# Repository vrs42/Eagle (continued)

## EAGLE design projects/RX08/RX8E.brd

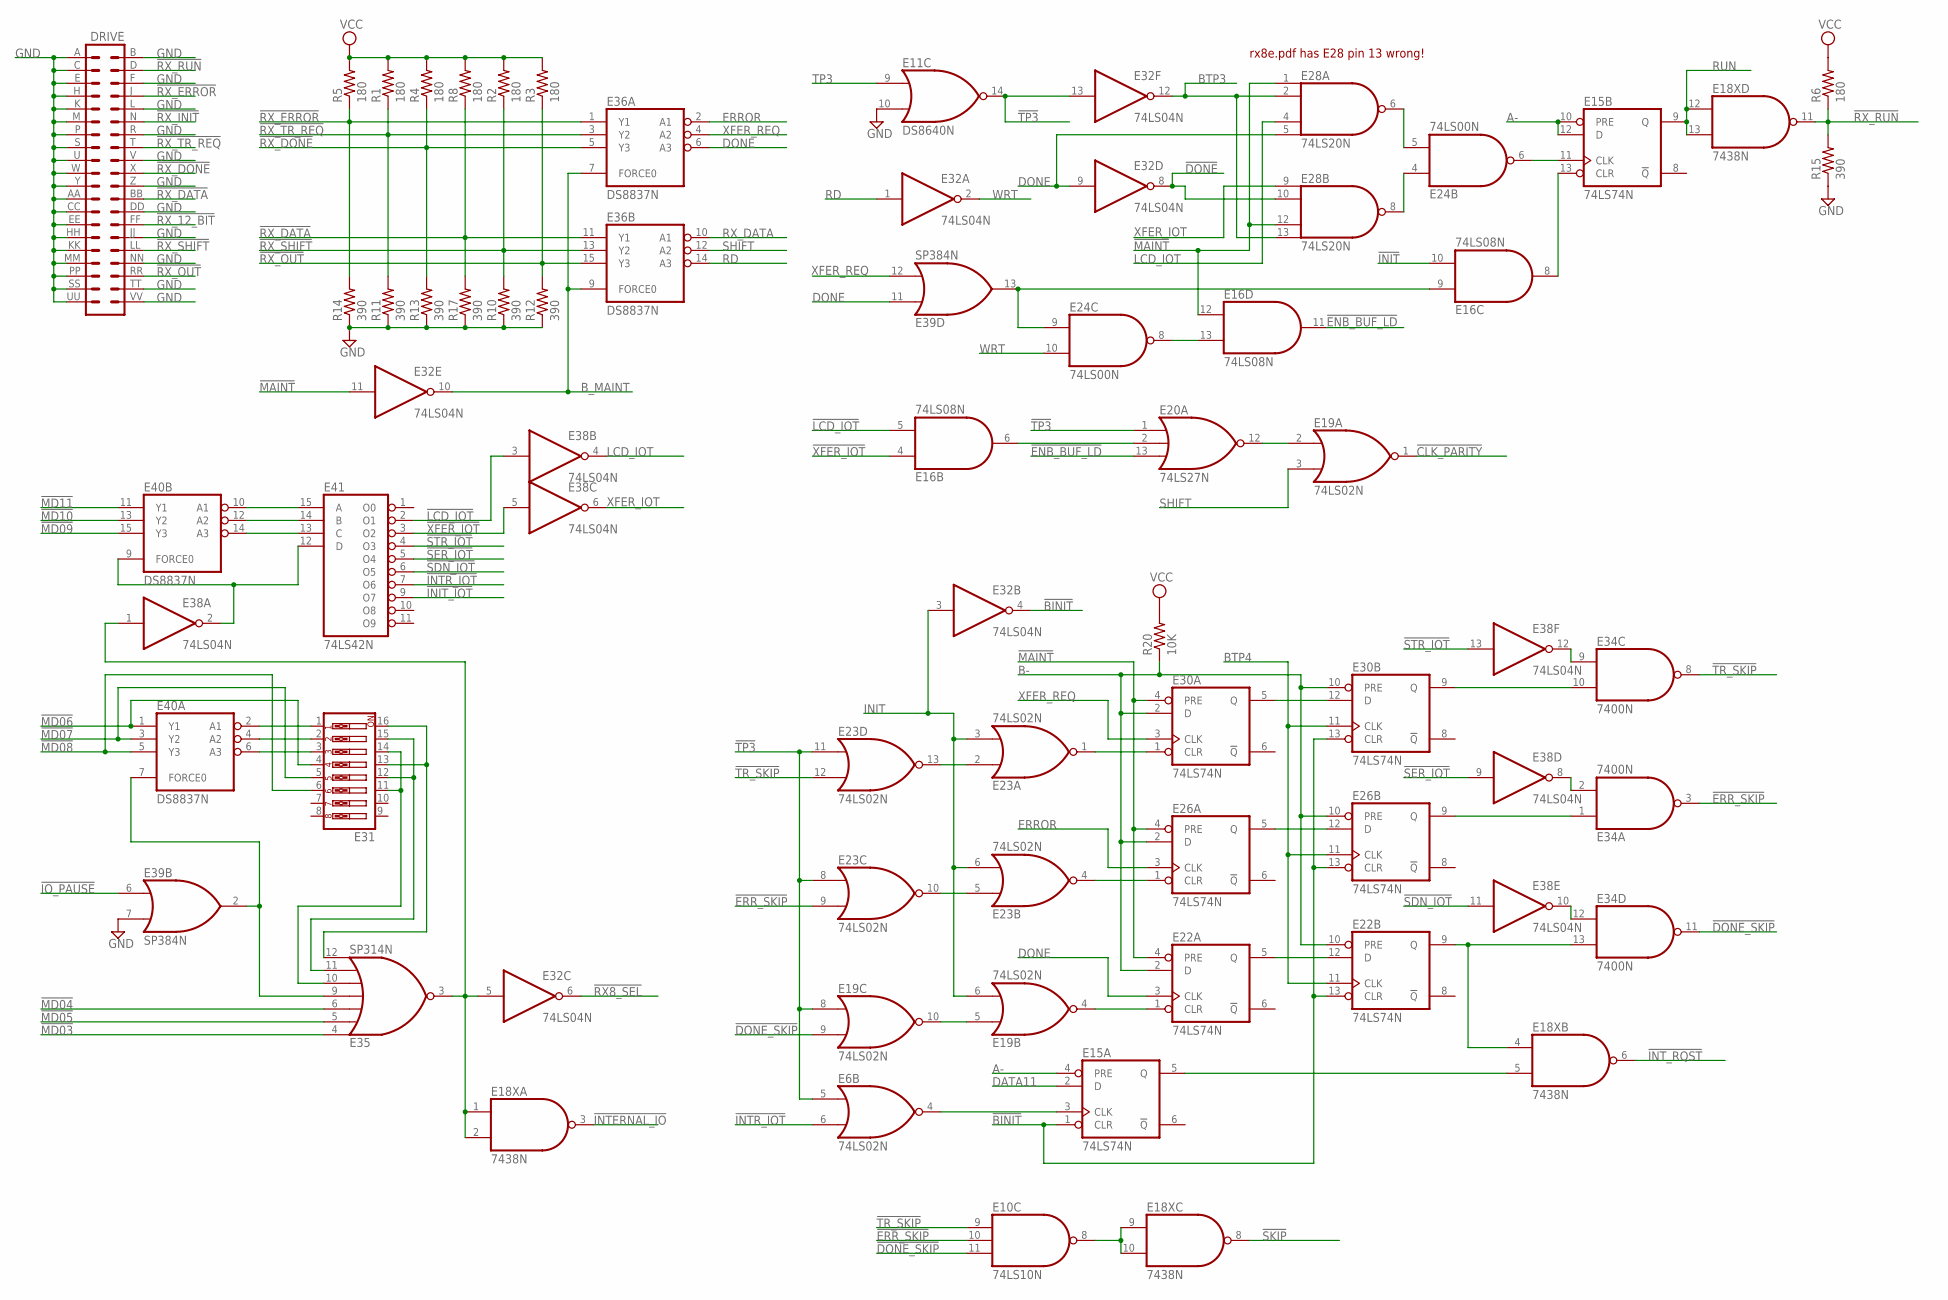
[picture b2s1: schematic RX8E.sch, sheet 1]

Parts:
DRIVE: DEC40PINH
E6, E19, E23: 74LS02N; DIL14
E10: 74LS10N; DIL14
E11: DS8640N; DIL14
E15, E22, E26, E30: 74LS74N; DIL14
E16: 74LS08N; DIL14
E18X: 7438N; DIL14
E20: 74LS27N; DIL14
E24: 74LS00N; DIL14
E28: 74LS20N; DIL14
E31: SW_DIP-8; EDG-08
E32, E38: 74LS04N; DIL14
E34: 7400N; DIL14
E35: SP314N; DIL14
E36, E40: DS8837N; DIL16
E39: SP384N; DIL14
E41: 74LS42N; DIL16
R1, R2, R3, R4, R5, R6, R8: 180; 0207/10
R10, R11, R12, R13, R14, R15, R17: 390; 0207/10
R20: 10K; 0207/10

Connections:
!BINIT: E15.1 (CLR), E22.13 (CLR), E26.13 (CLR), E30.13 (CLR), E32.4 (O)
!CLK_PARITY: E19.1 (O); also elsewhere on the board
!DONE: E28.10 (I1), E32.8 (O); also elsewhere on the board
!DONE_SKIP: E10.11 (I2), E19.9 (I1), E34.11 (O); also elsewhere on the board
!ENB_BUF_LD: E16.11 (O), E20.13 (I2); also elsewhere on the board
!ERR_SKIP: E10.10 (I1), E23.9 (I1), E34.3 (O)
!INIT: E16.10 (I1); also elsewhere on the board
!INIT_IOT: E41.9 (O7); also elsewhere on the board
!INTERNAL_IO: E18X.3 (O); also elsewhere on the board
!INTR_IOT: E6.6 (I1), E41.7 (O6)
!INT_RQST: E18X.6 (O); also elsewhere on the board
!IO_PAUSE: E39.6 (I0); also elsewhere on the board
!LCD_IOT: E16.5 (I1), E38.3 (I), E41.2 (O1); also elsewhere on the board
!MAINT: E16.12 (I0), E22.4 (PRE), E26.4 (PRE), E28.1 (I0), E28.12 (I2), E30.4 (PRE), E32.11 (I); also elsewhere on the board
!MD03: E35.4 (I0); also elsewhere on the board
!MD04: E35.6 (I2); also elsewhere on the board
!MD05: E35.5 (I1); also elsewhere on the board
!MD06: E31.4, E40.1 (Y1); also elsewhere on the board
!MD07: E31.5, E40.3 (Y2); also elsewhere on the board
!MD08: E31.6, E40.5 (Y3); also elsewhere on the board
!MD09: E40.15 (Y3); also elsewhere on the board
!MD10: E40.13 (Y2); also elsewhere on the board
!MD11: E40.11 (Y1); also elsewhere on the board
!RX8_SEL: E32.6 (O); also elsewhere on the board
!RX_12_BIT: DRIVE.FF (28); also elsewhere on the board
!RX_DATA: DRIVE.BB (24), E36.11 (Y1), R8.1, R17.2; also elsewhere on the board
!RX_DONE: DRIVE.X (20), E36.5 (Y3), R4.1, R13.2
!RX_ERROR: DRIVE.J (8), E36.1 (Y1), R5.1, R14.2
!RX_INIT: DRIVE.N (12); also elsewhere on the board
!RX_OUT: DRIVE.RR (36), E36.15 (Y3), R3.1, R12.2
!RX_RUN: DRIVE.D (4), E18X.11 (O), R6.1, R15.2
!RX_SHIFT: DRIVE.LL (32), E36.13 (Y2), R2.1, R10.2
!RX_TR_REQ: DRIVE.T (16), E36.3 (Y2), R1.1, R11.2
!SDN_IOT: E38.11 (I), E41.6 (O5)
!SER_IOT: E38.9 (I), E41.5 (O4)
!SKIP: E18X.8 (O); also elsewhere on the board
!STR_IOT: E38.13 (I), E41.4 (O3)
!TP3: E6.5 (I0), E11.14 (O), E19.8 (I0), E20.1 (I0), E23.8 (I0), E23.11 (I0), E32.13 (I); also elsewhere on the board
!TR_SKIP: E10.9 (I0), E23.12 (I1), E34.8 (O); also elsewhere on the board
!XFER_IOT: E16.4 (I0), E38.5 (I), E41.3 (O2); also elsewhere on the board
A-: E15.4 (PRE), E15.10 (PRE), E15.12 (D); also elsewhere on the board
B-: E22.2 (D), E22.10 (PRE), E26.2 (D), E26.10 (PRE), E30.2 (D), E30.10 (PRE), R20.1; also elsewhere on the board
BTP3: E28.2 (I1), E28.13 (I3), E32.12 (O); also elsewhere on the board
BTP4: E22.11 (CLK), E26.11 (CLK), E30.11 (CLK); also elsewhere on the board
B_MAINT: E32.10 (O), E36.7 (FORCE0), E36.9 (FORCE0)
DATA11: E15.2 (D); also elsewhere on the board
DONE: E22.3 (CLK), E28.5 (I3), E32.9 (I), E36.6 (A3), E39.11 (I0); also elsewhere on the board
ERROR: E26.3 (CLK), E36.2 (A1)
GND: DRIVE.A (1), DRIVE.AA (23), DRIVE.B (2), DRIVE.C (3), DRIVE.CC (25), DRIVE.DD (26), DRIVE.E (5), DRIVE.EE (27), DRIVE.F (6), DRIVE.H (7), DRIVE.HH (29), DRIVE.JJ (30), DRIVE.K (9), DRIVE.KK (31), DRIVE.L (10), DRIVE.M (11), DRIVE.MM (33), DRIVE.NN (34), DRIVE.P (13), DRIVE.PP (35), DRIVE.R (14), DRIVE.S (15), DRIVE.SS (37), DRIVE.TT (38), DRIVE.U (17), DRIVE.UU (39), DRIVE.V (18), DRIVE.VV (40), DRIVE.W (19), DRIVE.Y (21), DRIVE.Z (22), E6.7 (GND), E10.7 (GND), E11.1 (GND), E11.10 (I1), E15.7 (GND), E16.7 (GND), E18X.7 (GND), E19.7 (GND), E20.7 (GND), E22.7 (GND), E23.7 (GND), E24.7 (GND), E26.7 (GND), E28.7 (GND), E30.7 (GND), E32.7 (GND), E34.7 (GND), E35.1 (GND), E36.8 (GND), E38.7 (GND), E39.1 (GND), E39.7 (I1), E40.8 (GND), E41.8 (GND), R10.1, R11.1, R12.1, R13.1, R14.1, R15.1, R17.1; also elsewhere on the board
INIT: E19.6 (I1), E23.3 (I1), E23.6 (I1), E32.3 (I); also elsewhere on the board
LCD_IOT: E28.4 (I2), E38.4 (O); also elsewhere on the board
unnamed: E31.11, E31.14, E35.10 (I4)
unnamed: E31.12, E31.15, E35.11 (I5)
unnamed: E31.13, E31.16, E35.12 (I6)
unnamed: E31.3, E40.6 (A3)
unnamed: E31.2, E40.4 (A2)
unnamed: E31.1, E40.2 (A1)
unnamed: E35.9 (I3), E39.2 (O), E40.7 (FORCE0)
unnamed: E18X.1 (I0), E18X.2 (I1), E32.5 (I), E35.3 (O), E38.1 (I)
unnamed: E19.5 (I0), E19.10 (O)
unnamed: E38.2 (O), E40.9 (FORCE0), E41.12 (D)
unnamed: E40.14 (A3), E41.13 (C)
unnamed: E40.12 (A2), E41.14 (B)
unnamed: E40.10 (A1), E41.15 (A)
unnamed: E19.4 (O), E22.1 (CLR)
unnamed: E23.4 (O), E26.1 (CLR)
unnamed: E23.5 (I0), E23.10 (O)
unnamed: E23.2 (I0), E23.13 (O)
unnamed: E23.1 (O), E30.1 (CLR)
unnamed: E30.5 (Q), E30.12 (D)
unnamed: E26.5 (Q), E26.12 (D)
unnamed: E22.5 (Q), E22.12 (D)
unnamed: E18X.4 (I0), E22.9 (Q), E34.13 (I1)
unnamed: E26.9 (Q), E34.1 (I0)
unnamed: E6.4 (O), E15.3 (CLK)
unnamed: E30.9 (Q), E34.10 (I1)
unnamed: E34.2 (I1), E38.8 (O)
unnamed: E34.12 (I0), E38.10 (O)
unnamed: E34.9 (I0), E38.12 (O)
unnamed: E15.5 (Q), E18X.5 (I1)
unnamed: E10.8 (O), E18X.9 (I0), E18X.10 (I1)
unnamed: E24.5 (I1), E28.6 (O)
unnamed: E16.6 (O), E20.2 (I1)
unnamed: E24.4 (I0), E28.8 (O)
unnamed: E16.9 (I0), E24.9 (I0), E39.13 (O)
unnamed: E16.13 (I1), E24.8 (O)
unnamed: E15.13 (CLR), E16.8 (O)
unnamed: E19.2 (I0), E20.12 (O)
unnamed: E15.11 (CLK), E24.6 (O)
RD: E32.1 (I), E36.14 (A3); also elsewhere on the board
RUN: E15.9 (Q), E18X.12 (I0), E18X.13 (I1); also elsewhere on the board
RX_DATA: E36.10 (A1); also elsewhere on the board
SHIFT: E19.3 (I1), E36.12 (A2)
TP3: E11.9 (I0); also elsewhere on the board
VCC: E6.14 (VCC), E10.14 (VCC), E11.8 (VCC), E15.14 (VCC), E16.14 (VCC), E18X.14 (VCC), E19.14 (VCC), E20.14 (VCC), E22.14 (VCC), E23.14 (VCC), E24.14 (VCC), E26.14 (VCC), E28.14 (VCC), E30.14 (VCC), E32.14 (VCC), E34.14 (VCC), E35.8 (VCC), E36.16 (VCC), E38.14 (VCC), E39.8 (VCC), E40.16 (VCC), E41.16 (VCC), R1.2, R2.2, R3.2, R4.2, R5.2, R6.2, R8.2, R20.2; also elsewhere on the board
WRT: E24.10 (I1), E32.2 (O); also elsewhere on the board
XFER_IOT: E28.9 (I0), E38.6 (O); also elsewhere on the board
XFER_REQ: E30.3 (CLK), E36.4 (A2), E39.12 (I1)

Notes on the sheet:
rx8e.pdf has E28 pin 13 wrong!

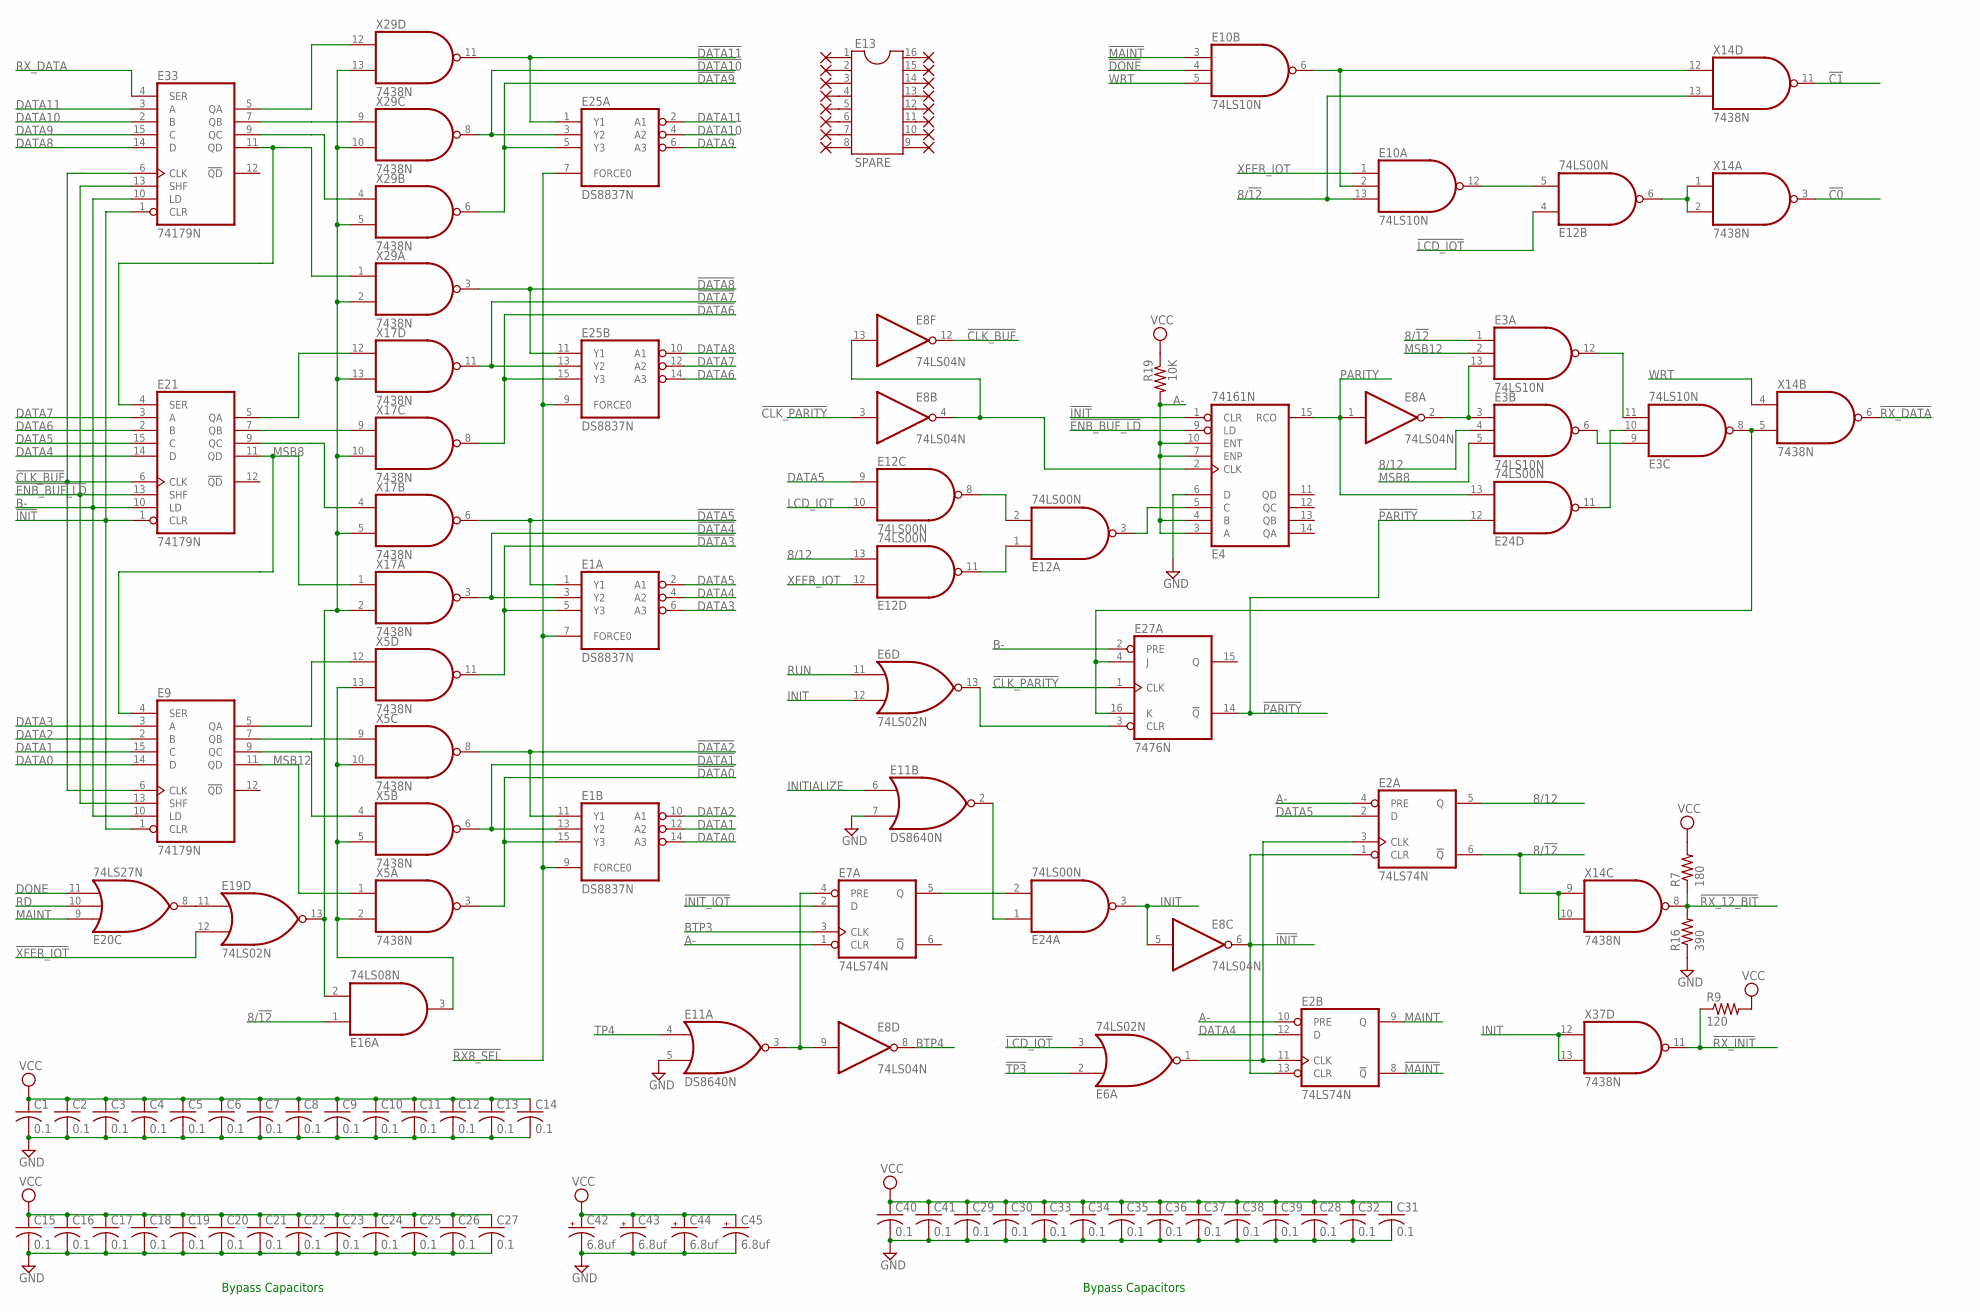
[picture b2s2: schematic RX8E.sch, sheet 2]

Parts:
C1, C2, C3, C4, C5, C6, C7, C8, C9, C10, C11, C12, C13, C14, C15, C16, C17, C18, C19, C20, C21, C22, C23, C24, C25, C26, C27, C28, C29, C30, C31, C32, C33, C34, C35, C36, C37, C38, C39, C40, C41: 0.1; C050-025X075
C42, C43, C44, C45: 6.8uf; E22-6
E1, E25: DS8837N; DIL16
E2, E7: 74LS74N; DIL14
E3, E10: 74LS10N; DIL14
E4: 74161N; DIL16
E6, E19: 74LS02N; DIL14
E8: 74LS04N; DIL14
E9, E21, E33: 74179N; DIL16
E11: DS8640N; DIL14
E12, E24: 74LS00N; DIL14
E13: SPARE; DIL16
E16: 74LS08N; DIL14
E20: 74LS27N; DIL14
E27: 7476N; DIL16
PAD10, PAD11, PAD12, PAD13, PAD14, PAD15, PAD16, PAD17, PAD20, PAD21, PAD22, PAD23, PAD24, PAD25, PAD26, PAD27: 1,6/0,8
R7: 180; 0207/10
R9: 120; 0207/10
R16: 390; 0207/10
R19: 10K; 0207/10
X5, X14, X17, X29, X37: 7438N; DIL14

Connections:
8/12: E2.5 (Q), E3.4 (I1), E12.13 (I1)
8/!12: E2.6 (!Q), E3.1 (I0), E10.13 (I2), E16.1 (I0), X14.9 (I0), X14.10 (I1), X14.13 (I1)
!C0: X14.3 (O); also elsewhere on the board
!C1: X14.11 (O); also elsewhere on the board
!CLK_BUF: E8.12 (O), E9.6 (CLK), E21.6 (CLK), E33.6 (CLK)
!CLK_PARITY: E8.3 (I), E27.1 (CLK); also elsewhere on the board
!DATA0: E1.15 (Y3), X5.3 (O); also elsewhere on the board
!DATA1: E1.13 (Y2), X5.6 (O); also elsewhere on the board
!DATA2: E1.11 (Y1), X5.8 (O); also elsewhere on the board
!DATA3: E1.5 (Y3), X5.11 (O); also elsewhere on the board
!DATA4: E1.3 (Y2), X17.3 (O); also elsewhere on the board
!DATA5: E1.1 (Y1), X17.6 (O); also elsewhere on the board
!DATA6: E25.15 (Y3), X17.8 (O); also elsewhere on the board
!DATA7: E25.13 (Y2), X17.11 (O); also elsewhere on the board
!DATA8: E25.11 (Y1), X29.3 (O); also elsewhere on the board
!DATA9: E25.5 (Y3), X29.6 (O); also elsewhere on the board
!DATA10: E25.3 (Y2), X29.8 (O); also elsewhere on the board
!DATA11: E25.1 (Y1), X29.11 (O); also elsewhere on the board
!DONE: E10.4 (I1); also elsewhere on the board
!ENB_BUF_LD: E4.9 (LD), E9.13 (SHF), E21.13 (SHF), E33.13 (SHF); also elsewhere on the board
!INIT: E2.1 (CLR), E2.13 (CLR), E4.1 (CLR), E8.6 (O), E9.1 (CLR), E21.1 (CLR), E33.1 (CLR); also elsewhere on the board
!INIT_IOT: E7.2 (D); also elsewhere on the board
!LCD_IOT: E6.3 (I1), E12.4 (I0); also elsewhere on the board
!MAINT: E2.8 (!Q), E10.3 (I0); also elsewhere on the board
!PARITY: E24.12 (I0), E27.14 (!Q)
!RX8_SEL: E1.7 (FORCE0), E1.9 (FORCE0), E25.7 (FORCE0), E25.9 (FORCE0); also elsewhere on the board
!RX_12_BIT: R7.1, R16.2, X14.8 (O); also elsewhere on the board
!RX_DATA: X14.6 (O); also elsewhere on the board
!RX_INIT: R9.1, X37.11 (O); also elsewhere on the board
!TP3: E6.2 (I0); also elsewhere on the board
!XFER_IOT: E19.12 (I1); also elsewhere on the board
A-: E2.4 (PRE), E2.10 (PRE), E4.3 (A), E4.4 (B), E4.7 (ENP), E4.10 (ENT), E7.1 (CLR), R19.2; also elsewhere on the board
B-: E9.10 (LD), E21.10 (LD), E27.2 (PRE), E33.10 (LD); also elsewhere on the board
BTP3: E7.3 (CLK); also elsewhere on the board
BTP4: E8.8 (O); also elsewhere on the board
DATA0: E1.14 (A3), E9.14 (D)
DATA1: E1.12 (A2), E9.15 (C)
DATA2: E1.10 (A1), E9.2 (B)
DATA3: E1.6 (A3), E9.3 (A)
DATA4: E1.4 (A2), E2.12 (D), E21.14 (D)
DATA5: E1.2 (A1), E2.2 (D), E12.9 (I0), E21.15 (C)
DATA6: E21.2 (B), E25.14 (A3)
DATA7: E21.3 (A), E25.12 (A2)
DATA8: E25.10 (A1), E33.14 (D)
DATA9: E25.6 (A3), E33.15 (C)
DATA10: E25.4 (A2), E33.2 (B)
DATA11: E25.2 (A1), E33.3 (A); also elsewhere on the board
DONE: E20.11 (I2); also elsewhere on the board
GND: C1.2, C2.2, C3.2, C4.2, C5.2, C6.2, C7.2, C8.2, C9.2, C10.2, C11.2, C12.2, C13.2, C14.2, C15.2, C16.2, C17.2, C18.2, C19.2, C20.2, C21.2, C22.2, C23.2, C24.2, C25.2, C26.2, C27.2, C28.2, C29.2, C30.2, C31.2, C32.2, C33.2, C34.2, C35.2, C36.2, C37.2, C38.2, C39.2, C40.2, C41.2, C42.-, C43.-, C44.-, C45.-, E1.8 (GND), E2.7 (GND), E3.7 (GND), E4.6 (D), E4.8 (GND), E6.7 (GND), E7.7 (GND), E8.7 (GND), E9.8 (GND), E10.7 (GND), E11.1 (GND), E11.5 (I1), E11.7 (I1), E12.7 (GND), E16.7 (GND), E19.7 (GND), E20.7 (GND), E21.8 (GND), E24.7 (GND), E25.8 (GND), E27.13 (GND), E33.8 (GND), R16.1, X5.7 (GND), X14.7 (GND), X17.7 (GND), X29.7 (GND), X37.7 (GND); also elsewhere on the board
INIT: E6.12 (I1), E8.5 (I), E24.3 (O), X37.12 (I0), X37.13 (I1); also elsewhere on the board
INITIALIZE: E11.6 (I0); also elsewhere on the board
LCD_IOT: E12.10 (I1); also elsewhere on the board
MAINT: E2.9 (Q), E20.9 (I0)
MSB8: E3.5 (I2), E9.4 (SER), E21.11 (QD), X17.1 (I0)
MSB12: E3.2 (I1), E9.11 (QD), X5.1 (I0)
unnamed: E9.7 (QB), X5.9 (I0)
unnamed: E16.2 (I1), E19.13 (O), X17.2 (I1), X17.5 (I1), X17.10 (I1), X17.13 (I1), X29.2 (I1), X29.5 (I1), X29.10 (I1), X29.13 (I1)
unnamed: E19.11 (I0), E20.8 (O)
unnamed: E16.3 (O), X5.2 (I1), X5.5 (I1), X5.10 (I1), X5.13 (I1)
unnamed: E13.1, PAD10.1
unnamed: E13.2, PAD11.1
unnamed: E13.3, PAD12.1
unnamed: E13.4, PAD13.1
unnamed: E13.5, PAD14.1
unnamed: E13.6, PAD15.1
unnamed: E13.7, PAD16.1
unnamed: E13.8, PAD17.1
unnamed: E4.5 (C), E12.3 (O)
unnamed: E12.6 (O), X14.1 (I0), X14.2 (I1)
unnamed: E13.16, PAD20.1
unnamed: E13.15, PAD21.1
unnamed: E13.14, PAD22.1
unnamed: E13.13, PAD23.1
unnamed: E13.12, PAD24.1
unnamed: E13.11, PAD25.1
unnamed: E13.10, PAD26.1
unnamed: E13.9, PAD27.1
unnamed: E21.4 (SER), E33.11 (QD), X29.1 (I0)
unnamed: E10.12 (O), E12.5 (I1)
unnamed: E9.9 (QC), X5.4 (I0)
unnamed: E10.2 (I1), E10.6 (O), X14.12 (I0)
unnamed: E12.1 (I0), E12.11 (O)
unnamed: E12.2 (I1), E12.8 (O)
unnamed: E3.3 (I0), E3.13 (I2), E8.2 (O)
unnamed: E3.11 (I2), E3.12 (O)
unnamed: E3.6 (O), E3.9 (I0)
unnamed: E3.10 (I1), E24.11 (O)
unnamed: E3.8 (O), E27.4 (J), E27.16 (K), X14.5 (I1)
unnamed: E7.4 (PRE), E8.9 (I), E11.3 (O)
unnamed: E4.2 (CLK), E8.4 (O), E8.13 (I)
unnamed: E7.5 (Q), E24.2 (I1)
unnamed: E6.13 (O), E27.3 (CLR)
unnamed: E11.2 (O), E24.1 (I0)
unnamed: E2.3 (CLK), E2.11 (CLK), E6.1 (O)
unnamed: E9.5 (QA), X5.12 (I0)
unnamed: E21.9 (QC), X17.4 (I0)
unnamed: E21.7 (QB), X17.9 (I0)
unnamed: E21.5 (QA), X17.12 (I0)
unnamed: E33.5 (QA), X29.12 (I0)
unnamed: E33.9 (QC), X29.4 (I0)
unnamed: E33.7 (QB), X29.9 (I0)
PARITY: E4.15 (RCO), E8.1 (I), E24.13 (I1); also elsewhere on the board
RD: E20.10 (I1); also elsewhere on the board
RUN: E6.11 (I0); also elsewhere on the board
RX_DATA: E33.4 (SER); also elsewhere on the board
TP4: E11.4 (I0); also elsewhere on the board
VCC: C1.1, C2.1, C3.1, C4.1, C5.1, C6.1, C7.1, C8.1, C9.1, C10.1, C11.1, C12.1, C13.1, C14.1, C15.1, C16.1, C17.1, C18.1, C19.1, C20.1, C21.1, C22.1, C23.1, C24.1, C25.1, C26.1, C27.1, C28.1, C29.1, C30.1, C31.1, C32.1, C33.1, C34.1, C35.1, C36.1, C37.1, C38.1, C39.1, C40.1, C41.1, C42.+, C43.+, C44.+, C45.+, E1.16 (VCC), E2.14 (VCC), E3.14 (VCC), E4.16 (VCC), E6.14 (VCC), E7.14 (VCC), E8.14 (VCC), E9.16 (VCC), E10.14 (VCC), E11.8 (VCC), E12.14 (VCC), E16.14 (VCC), E19.14 (VCC), E20.14 (VCC), E21.16 (VCC), E24.14 (VCC), E25.16 (VCC), E27.5 (VCC), E33.16 (VCC), R7.2, R9.2, R19.1, X5.14 (VCC), X14.14 (VCC), X17.14 (VCC), X29.14 (VCC), X37.14 (VCC); also elsewhere on the board
WRT: E10.5 (I2), X14.4 (I0); also elsewhere on the board
XFER_IOT: E10.1 (I0), E12.12 (I0); also elsewhere on the board

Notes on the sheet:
Bypass Capacitors

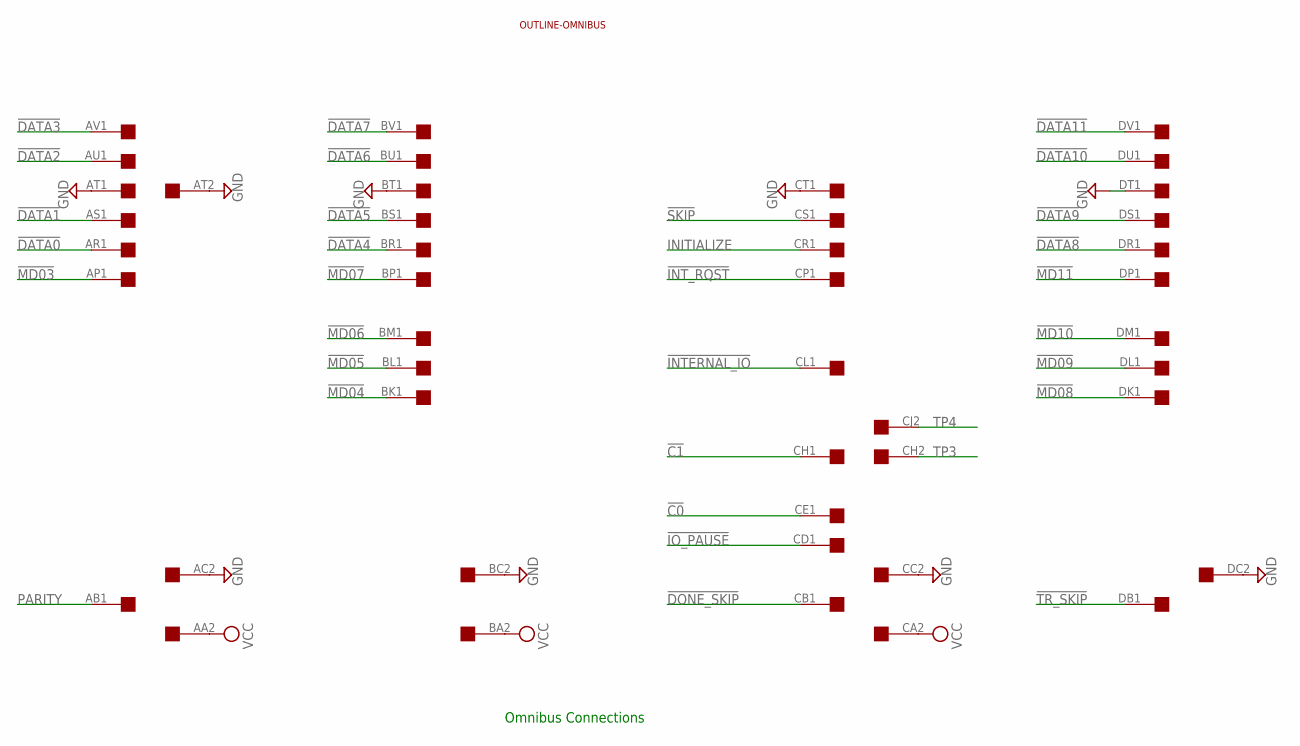
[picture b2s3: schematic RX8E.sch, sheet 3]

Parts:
U$2: QUAD; EDGE-CON8
U$5: OUTLINE-OMNIBUS; OMNIBUS

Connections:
!C0: U$2.CE1; also elsewhere on the board
!C1: U$2.CH1; also elsewhere on the board
!DATA0: U$2.AR1; also elsewhere on the board
!DATA1: U$2.AS1; also elsewhere on the board
!DATA2: U$2.AU1; also elsewhere on the board
!DATA3: U$2.AV1; also elsewhere on the board
!DATA4: U$2.BR1; also elsewhere on the board
!DATA5: U$2.BS1; also elsewhere on the board
!DATA6: U$2.BU1; also elsewhere on the board
!DATA7: U$2.BV1; also elsewhere on the board
!DATA8: U$2.DR1; also elsewhere on the board
!DATA9: U$2.DS1; also elsewhere on the board
!DATA10: U$2.DU1; also elsewhere on the board
!DATA11: U$2.DV1; also elsewhere on the board
!DONE_SKIP: U$2.CB1; also elsewhere on the board
!INTERNAL_IO: U$2.CL1; also elsewhere on the board
!INT_RQST: U$2.CP1; also elsewhere on the board
!IO_PAUSE: U$2.CD1; also elsewhere on the board
!MD03: U$2.AP1; also elsewhere on the board
!MD04: U$2.BK1; also elsewhere on the board
!MD05: U$2.BL1; also elsewhere on the board
!MD06: U$2.BM1; also elsewhere on the board
!MD07: U$2.BP1; also elsewhere on the board
!MD08: U$2.DK1; also elsewhere on the board
!MD09: U$2.DL1; also elsewhere on the board
!MD10: U$2.DM1; also elsewhere on the board
!MD11: U$2.DP1; also elsewhere on the board
!SKIP: U$2.CS1; also elsewhere on the board
!TR_SKIP: U$2.DB1; also elsewhere on the board
GND: U$2.AC2, U$2.AT1, U$2.AT2, U$2.BC2, U$2.BT1, U$2.CC2, U$2.CT1, U$2.DC2, U$2.DT1; also elsewhere on the board
INITIALIZE: U$2.CR1; also elsewhere on the board
PARITY: U$2.AB1; also elsewhere on the board
TP3: U$2.CH2; also elsewhere on the board
TP4: U$2.CJ2; also elsewhere on the board
VCC: U$2.AA2, U$2.BA2, U$2.CA2; also elsewhere on the board

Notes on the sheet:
Omnibus Connections

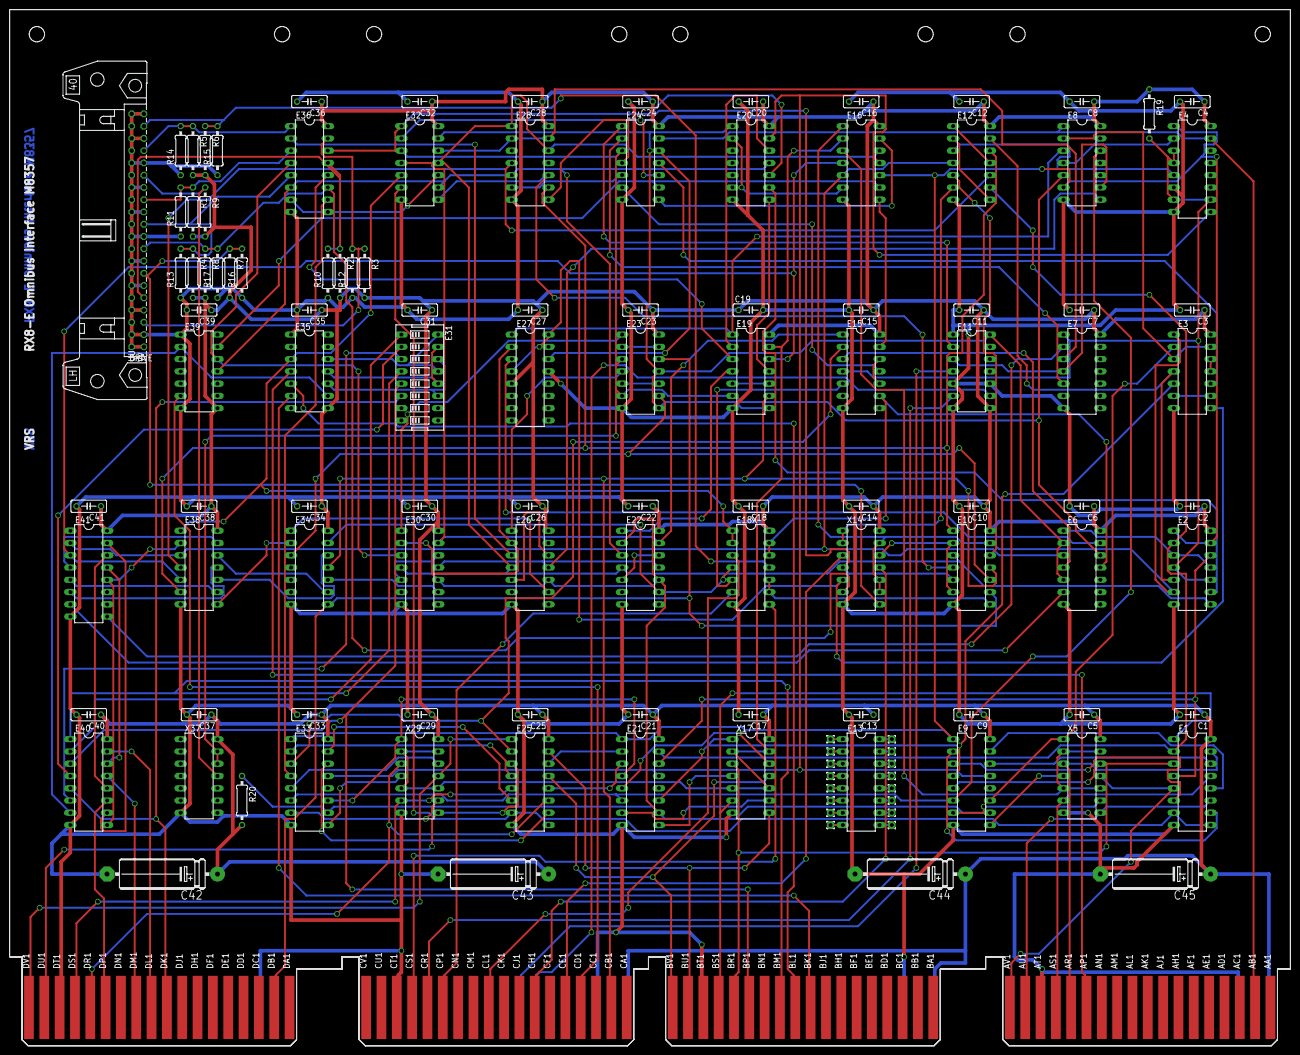
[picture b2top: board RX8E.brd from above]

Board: 2 copper layers, 265.3 x 214.6 mm, 124 parts (0 on the bottom side), 179 nets.
